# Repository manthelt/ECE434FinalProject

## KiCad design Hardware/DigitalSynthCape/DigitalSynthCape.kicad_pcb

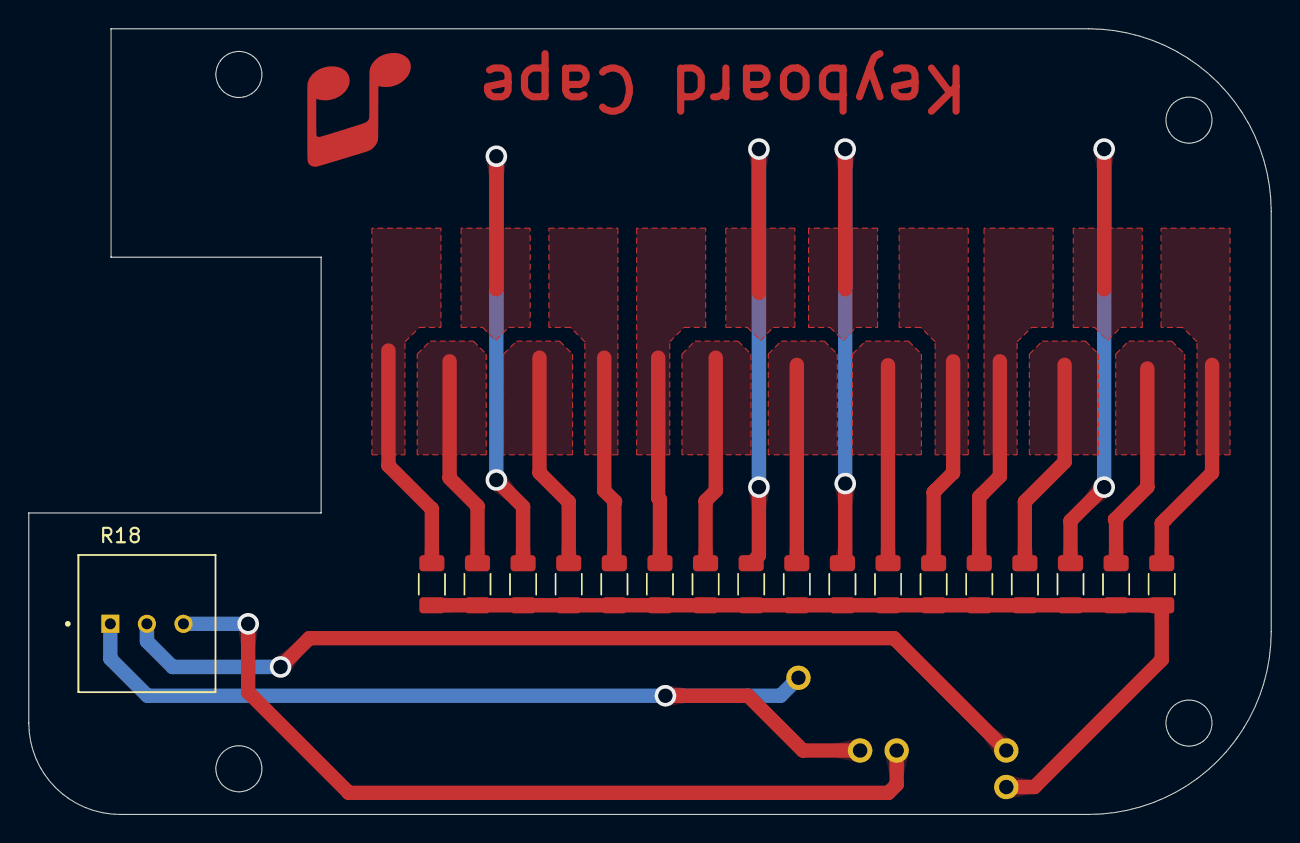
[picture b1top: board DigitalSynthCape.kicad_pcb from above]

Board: 2 copper layers, 86.4 x 54.6 mm, 23 parts (0 on the bottom side), 4 nets.

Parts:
MH1, MH2, MH3, MH4: MountingHole_3.2mm_M3_DIN965
P9: BeagleBone_Black_Header; PinHeader_2x23_P2.54mm_Vertical
R1, R2, R3, R4, R5, R6, R7, R8, R9, R10, R11, R12, R13, R14, R15, R16, R17: R; R_1206_3216Metric
R18: COM-09806; TRIM_COM-09806

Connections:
+1V8: P9.32, R18.1
/AIN0: P9.39, R1.2, R2.2, R3.2, R4.2, R5.2, R6.2, R7.2, R8.2, R9.2, R10.2, R11.2, R12.2, R13.2, R14.2, R15.2, R16.2, R17.2
/AIN1: P9.40, R18.2
GNDA: P9.34, R18.3

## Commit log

2023-09-20 Minor fixes and added setup file
2023-09-20 Recording server works
2023-09-20 Recording and playback working
2024-01-26 Starting Readme
2024-01-26 Started PCB
2024-01-26 Added Render
2024-01-26 Added Script to Create HTML Site from ReadMe for Export to Wiki
2024-01-29 Updates to PCB
2024-01-29 Test
2024-02-06 Orgainzed Stuff
2024-02-06 Added Software Readme
2024-02-08 Initial sound from potentiometer
2024-02-08 Added Gerbers
2024-02-08 Progress on sound
2024-02-14 Added Poster Stuff
2024-02-15 Added Some Amazing Tunes
2024-02-15 Progress on playing notes
2024-02-15 Updates to Readme
2024-02-20 Progress on flask server (not working)
2024-02-20 documentation stuff
2024-02-21 Basic flask and playing working, progress on recording
2024-02-21 readme
2024-02-21 more
2024-02-21 alsmot done
2024-02-21 Octave selection works
2024-02-21 Recording with octave and buttons working
2024-02-21 setup changes
2024-02-21 only need vid
2024-02-21 Exec summary
2024-02-21 readme edits
2024-02-21 video link
2024-02-21 sound thing instr
2024-02-22 Updated TOC
